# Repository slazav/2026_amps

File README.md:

A hobby project: basic electronics for my home lab (current and voltage amplifiers, current source)

https://slazav.xyz/lab/20260426-newamps.htm (RU)

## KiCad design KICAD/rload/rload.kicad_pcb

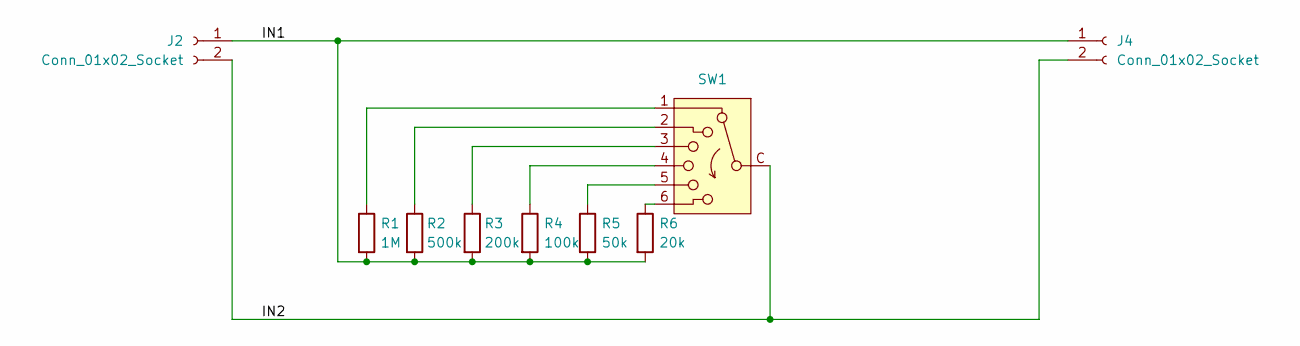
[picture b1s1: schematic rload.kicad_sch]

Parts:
J2, J4: Conn_01x02_Socket; conn_sig2
R1: 1M; R_0805_2012Metric
R2: 500k; R_0805_2012Metric
R3: 200k; R_0805_2012Metric
R4: 100k; R_0805_2012Metric
R5: 50k; R_0805_2012Metric
R6: 20k; R_0805_2012Metric
SW1: SW_Rotary_1x6_MP; switch6

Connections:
/IN1: J2.1, J4.1, R1.2, R2.2, R3.2, R4.2, R5.2, R6.2
/IN2: J2.2, J4.2, SW1.C
unnamed: R1.1, SW1.1
unnamed: R2.1, SW1.2
unnamed: R3.1, SW1.3
unnamed: R4.1, SW1.4
unnamed: R5.1, SW1.5
unnamed: R6.1, SW1.6

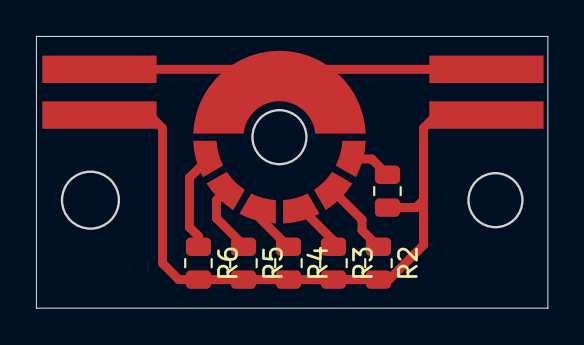
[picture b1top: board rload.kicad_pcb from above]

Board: 2 copper layers, 28.3 x 15.0 mm, 9 parts (0 on the bottom side), 8 nets.

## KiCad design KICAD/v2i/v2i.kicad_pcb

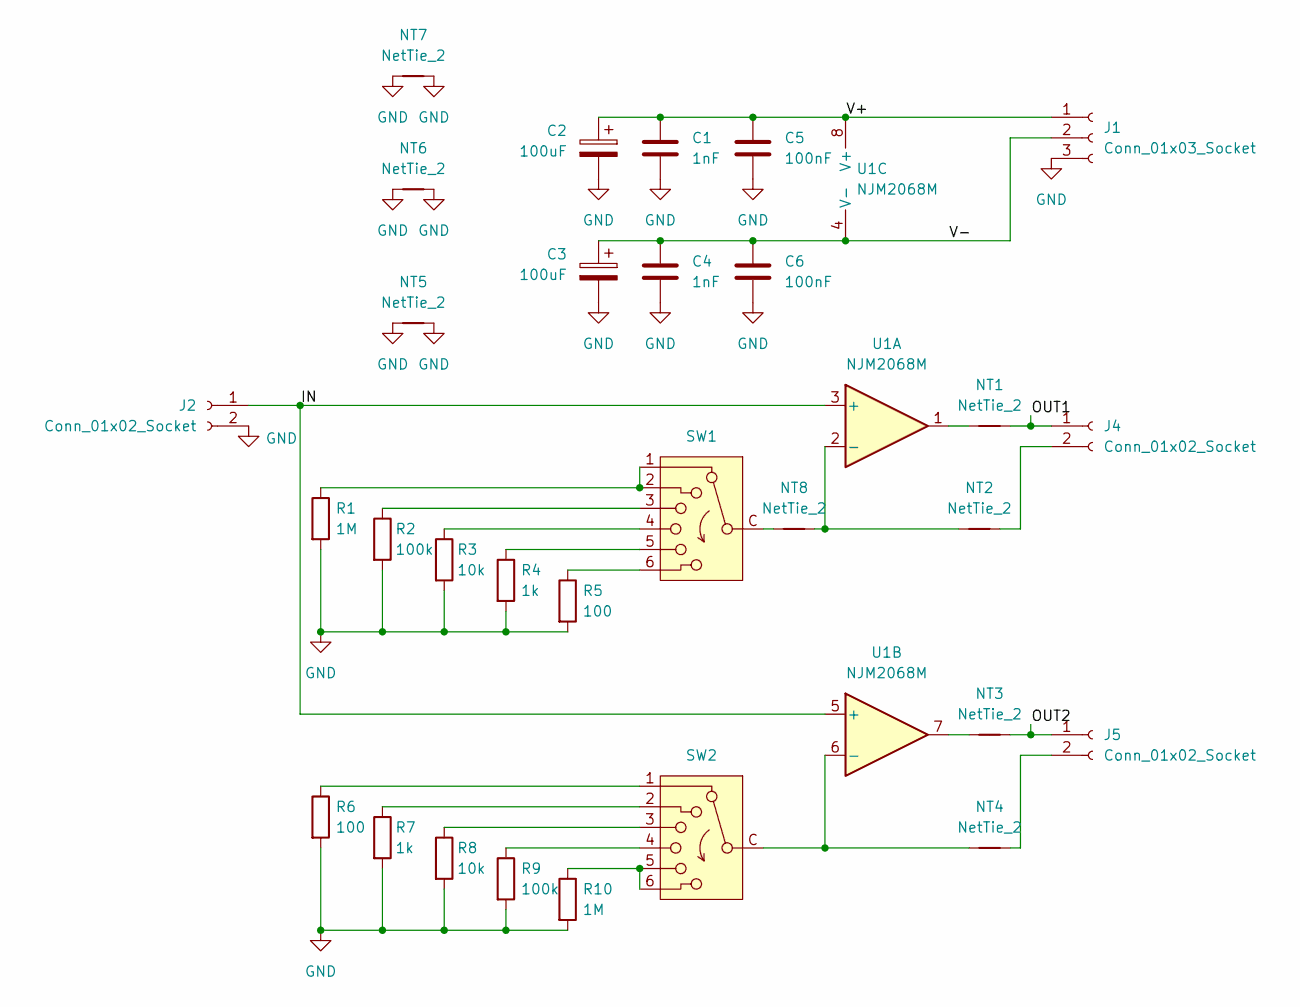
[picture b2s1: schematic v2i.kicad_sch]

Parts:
C1, C4: 1nF; C_0603_1608Metric
C2, C3: 100uF; C_1206_3216Metric
C5, C6: 100nF; C_0603_1608Metric
J1: Conn_01x03_Socket; conn_pwr3
J2, J4, J5: Conn_01x02_Socket; conn_sig2
NT1, NT2, NT3, NT4, NT5, NT6, NT7, NT8: NetTie_2; R_1206_3216Metric
R1, R10: 1M; R_0805_2012Metric
R2, R9: 100k; R_0805_2012Metric
R3, R8: 10k; R_0805_2012Metric
R4, R7: 1k; R_0805_2012Metric
R5, R6: 100; R_0805_2012Metric
SW1, SW2: SW_Rotary_1x6_MP; switch6
U1: NJM2068M; SOIC-8_5.3x5.3mm_P1.27mm

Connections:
/IN: J2.1, U1.3 (+), U1.5 (+)
/OUT1: J4.1, NT1.2
/OUT2: J5.1, NT3.2
/V+: C1.1, C2.1, C5.1, J1.1, U1.8 (V+)
/V-: C3.1, C4.1, C6.1, J1.2, U1.4 (V-)
GND: C1.2, C2.2, C3.2, C4.2, C5.2, C6.2, J1.3, J2.2, NT5.1, NT5.2, NT6.1, NT6.2, NT7.1, NT7.2, R1.2, R2.2, R3.2, R4.2, R5.2, R6.2, R7.2, R8.2, R9.2, R10.2
unnamed: J4.2, NT2.2
unnamed: J5.2, NT4.2
unnamed: NT1.1, U1.1
unnamed: NT3.1, U1.7
unnamed: NT8.1, SW1.C
unnamed: R1.1, SW1.1, SW1.2
unnamed: R2.1, SW1.3
unnamed: R3.1, SW1.4
unnamed: R4.1, SW1.5
unnamed: R5.1, SW1.6
unnamed: R6.1, SW2.1
unnamed: R7.1, SW2.2
unnamed: R8.1, SW2.3
unnamed: R9.1, SW2.4
unnamed: R10.1, SW2.5, SW2.6
unnamed: NT2.1, NT8.2, U1.2 (-)
unnamed: NT4.1, SW2.C, U1.6 (-)

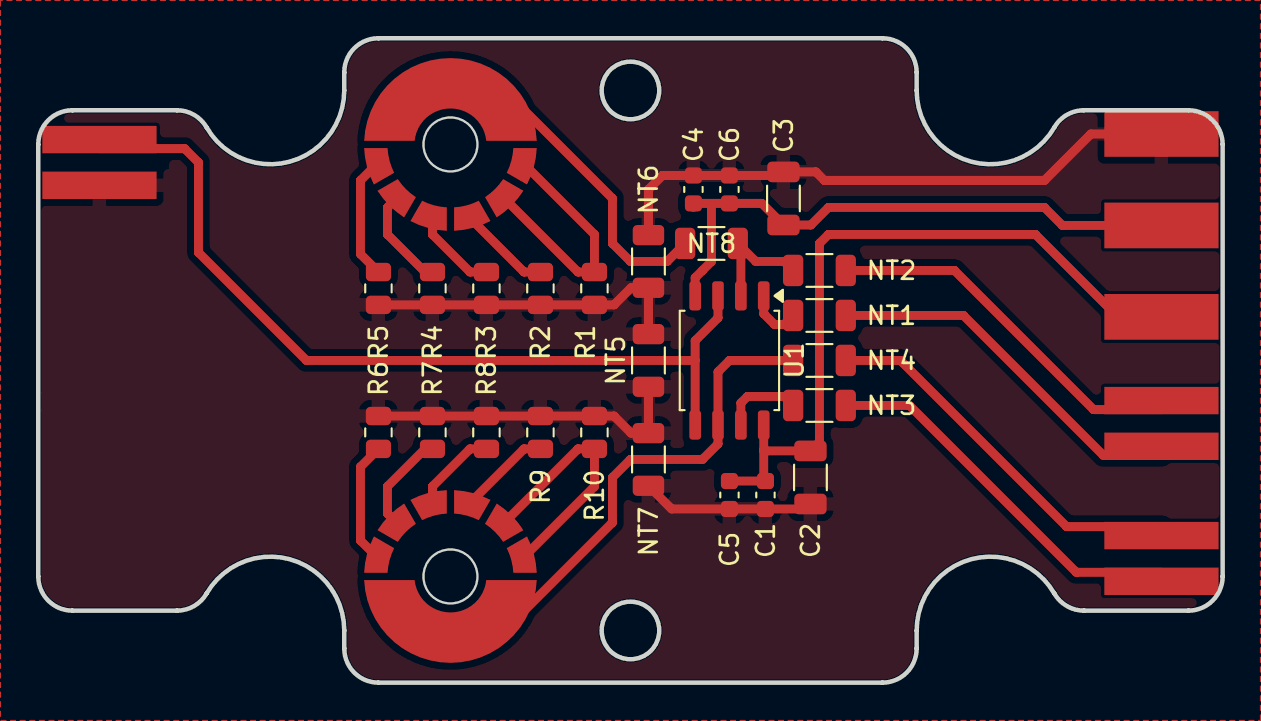
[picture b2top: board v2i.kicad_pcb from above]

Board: 2 copper layers, 65.8 x 35.8 mm, 31 parts (0 on the bottom side), 23 nets.

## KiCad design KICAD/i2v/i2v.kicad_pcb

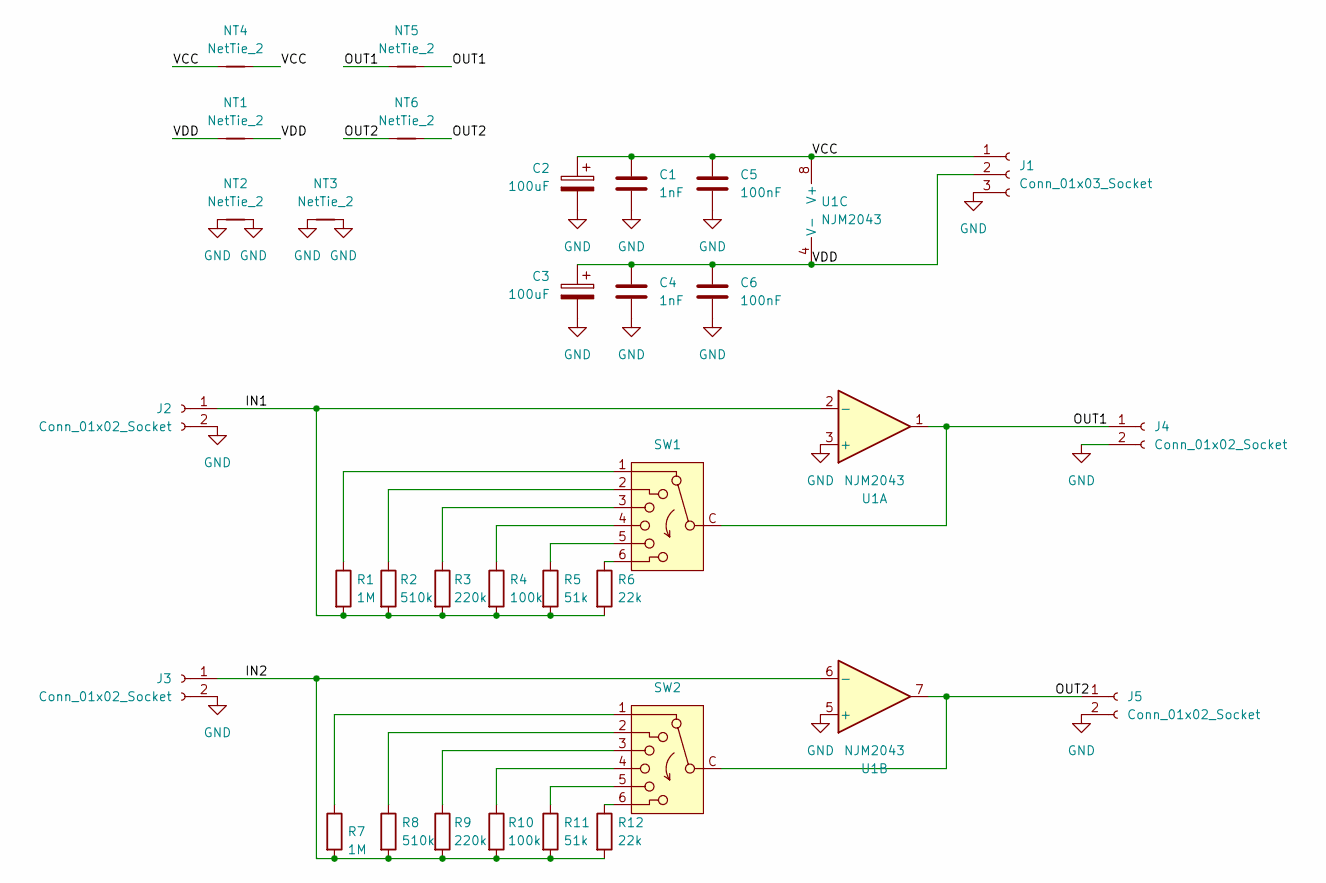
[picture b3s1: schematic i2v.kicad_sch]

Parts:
C1, C4: 1nF; C_0603_1608Metric
C2, C3: 100uF; C_1206_3216Metric
C5, C6: 100nF; C_0603_1608Metric
J1: Conn_01x03_Socket; conn_pwr3
J2, J3, J4, J5: Conn_01x02_Socket; conn_sig2
NT1, NT2, NT3, NT4, NT5, NT6: NetTie_2; R_1206_3216Metric
R1, R7: 1M; R_0805_2012Metric
R2, R8: 510k; R_0805_2012Metric
R3, R9: 220k; R_0805_2012Metric
R4, R10: 100k; R_0805_2012Metric
R5, R11: 51k; R_0805_2012Metric
R6, R12: 22k; R_0805_2012Metric
SW1, SW2: SW_Rotary_1x6_MP; switch6
U1: NJM2043; SOIC-8_5.3x5.3mm_P1.27mm

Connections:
/IN1: J2.1, R1.2, R2.2, R3.2, R4.2, R5.2, R6.2, U1.2 (-)
/IN2: J3.1, R7.2, R8.2, R9.2, R10.2, R11.2, R12.2, U1.6 (-)
/OUT1: J4.1, NT5.1, NT5.2, SW1.C, U1.1
/OUT2: J5.1, NT6.1, NT6.2, SW2.C, U1.7
/VCC: C1.1, C2.1, C5.1, J1.1, NT4.1, NT4.2, U1.8 (V+)
/VDD: C3.1, C4.1, C6.1, J1.2, NT1.1, NT1.2, U1.4 (V-)
GND: C1.2, C2.2, C3.2, C4.2, C5.2, C6.2, J1.3, J2.2, J3.2, J4.2, J5.2, NT2.1, NT2.2, NT3.1, NT3.2, U1.3 (+), U1.5 (+)
unnamed: R1.1, SW1.1
unnamed: R2.1, SW1.2
unnamed: R3.1, SW1.3
unnamed: R4.1, SW1.4
unnamed: R5.1, SW1.5
unnamed: R6.1, SW1.6
unnamed: R7.1, SW2.1
unnamed: R8.1, SW2.2
unnamed: R9.1, SW2.3
unnamed: R10.1, SW2.4
unnamed: R11.1, SW2.5
unnamed: R12.1, SW2.6

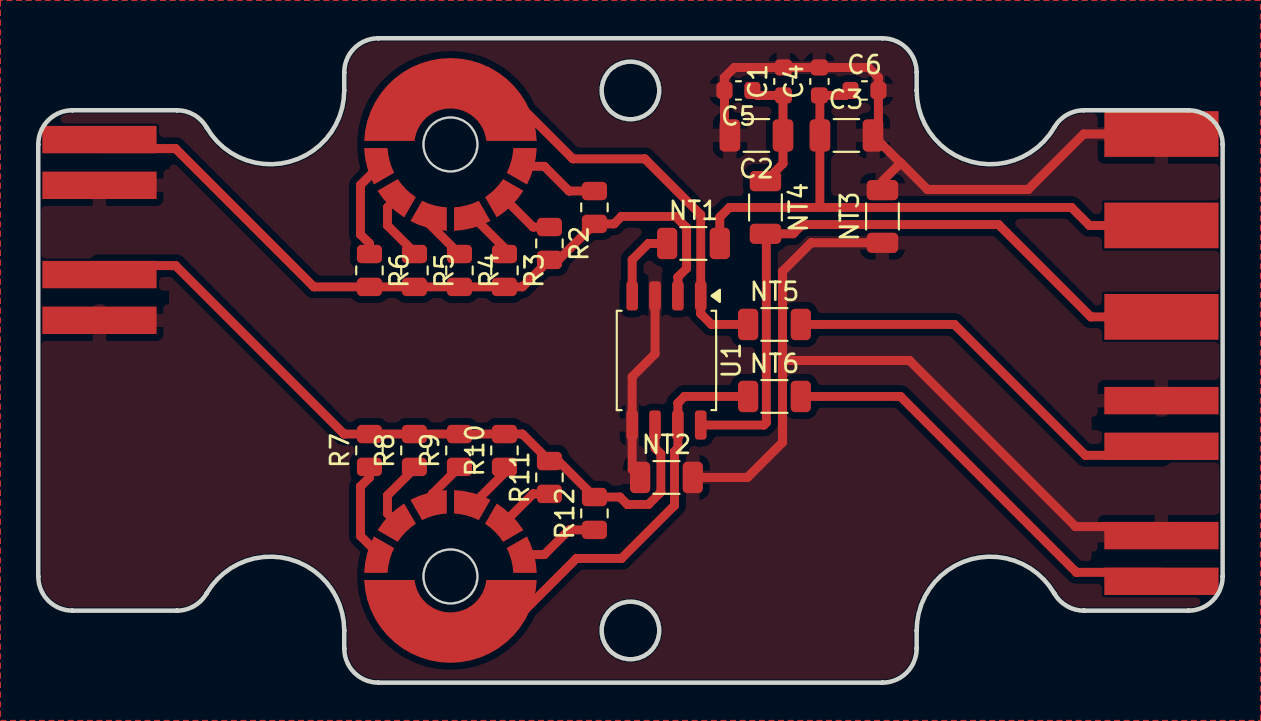
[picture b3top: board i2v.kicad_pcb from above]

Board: 2 copper layers, 65.8 x 35.8 mm, 32 parts (0 on the bottom side), 19 nets.

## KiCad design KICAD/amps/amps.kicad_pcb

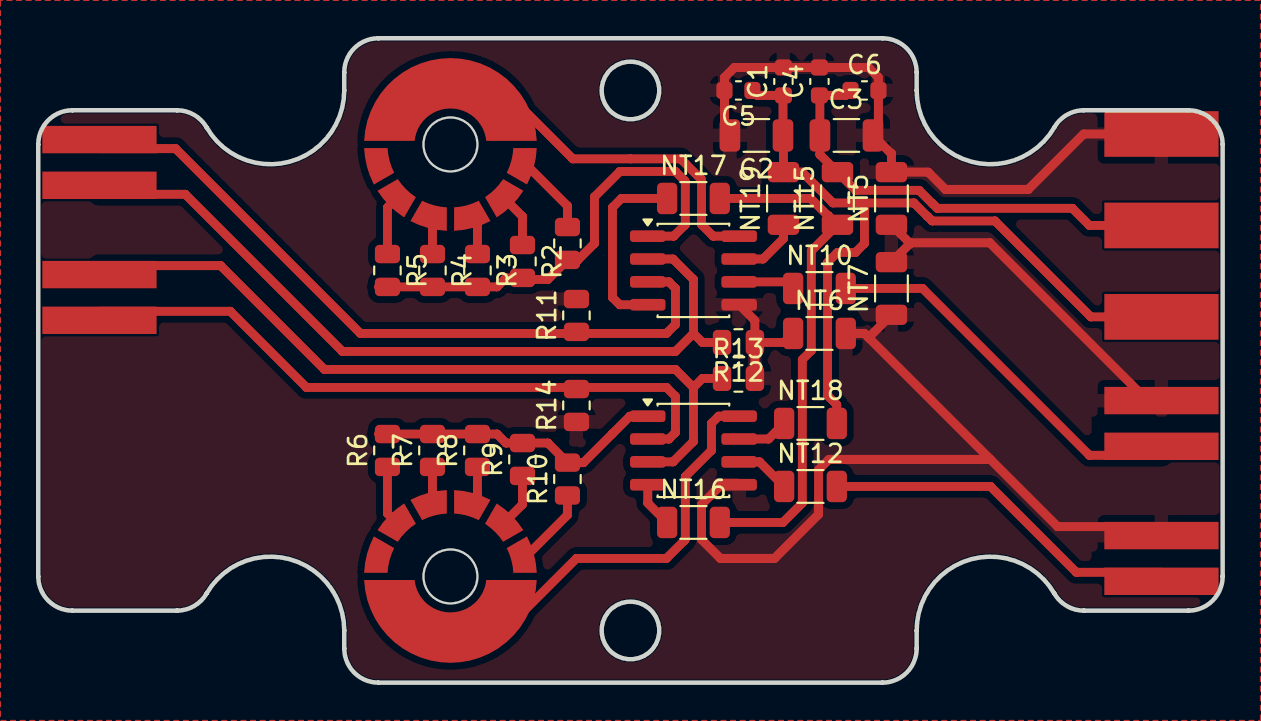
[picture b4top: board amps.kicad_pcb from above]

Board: 2 copper layers, 65.8 x 35.8 mm, 39 parts (0 on the bottom side), 25 nets.

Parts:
C1, C4: 1nF; C_0603_1608Metric
C2, C3: 100uF; C_1206_3216Metric
C5, C6: 100nF; C_0603_1608Metric
J1: Conn_01x03_Socket; conn_pwr3
J2, J3, J4, J5: Conn_01x02_Socket; conn_sig2
NT5, NT6, NT7, NT10, NT12, NT15, NT16, NT17, NT18, NT19: NetTie_2; R_1206_3216Metric
R1, R10: 5k; R_0805_2012Metric
R2, R9: 2k; R_0805_2012Metric
R3, R8: 500; R_0805_2012Metric
R4, R7: 200; R_0805_2012Metric
R5, R6: 50; R_0805_2012Metric
R11, R12, R13, R14: 1M; R_0805_2012Metric
SW1, SW2: SW_Rotary_1x6_MP; switch6
U1, U2: INA128; SOP-8_3.76x4.96mm_P1.27mm

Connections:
/IN1N: J2.2, R12.2, U1.2 (-)
/IN1P: J2.1, R11.1, U1.3 (+)
/IN2N: J3.2, R14.2, U2.2 (-)
/IN2P: J3.1, R13.1, U2.3 (+)
/OUT1: J4.1, NT10.2
/OUT2: J5.1, NT12.2
GND: C1.2, C2.2, C3.2, C4.2, C5.2, C6.2, J1.3, J4.2, J5.2, NT5.1, NT5.2, NT6.1, NT6.2, NT7.1, NT7.2, R11.2, R12.1, R13.2, R14.1, U1.5 (Ref), U2.5 (Ref)
unnamed: NT10.1, U1.6
unnamed: NT12.1, U2.6
unnamed: R1.1, SW1.1
unnamed: R1.2, R2.2, R3.2, R4.2, R5.2, U1.1 (Rg)
unnamed: R2.1, SW1.2
unnamed: R3.1, SW1.3
unnamed: R4.1, SW1.4
unnamed: R5.1, SW1.5
unnamed: R6.1, SW2.2
unnamed: R7.1, SW2.3
unnamed: R8.1, SW2.4
unnamed: R9.1, SW2.5
unnamed: R10.1, SW2.6
unnamed: R6.2, R7.2, R8.2, R9.2, R10.2, U2.1 (Rg)
unnamed: SW1.C, U1.8 (Rg)
unnamed: SW2.C, U2.8 (Rg)
VCC: C1.1, C2.1, C5.1, J1.1, NT18.1, NT18.2, NT19.1, NT19.2, U1.7 (V+), U2.7 (V+)
VDD: C3.1, C4.1, C6.1, J1.2, NT15.1, NT15.2, NT16.1, NT16.2, NT17.1, NT17.2, U1.4 (V-), U2.4 (V-)

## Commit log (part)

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2026-06-02 Add KiCAD files:
    This commit is done after making first version of the PCBs.
    A couple of fixes have been added compared to the fabricated version:
    - add missing switch pads in amps PCB
    - adjust connector pads
2026-06-02 add DXF files (boxes and PCB outlines)
2026-06-02 Create LICENSE
2026-06-02 add DXF_PCB (new version, not tested)
2026-06-02 add QUCS folder
2026-06-03 small fixes in KiCAD and DXF
2026-06-03 README.md: add link and image
2026-06-06 add measurement results for voltage amplifier
2026-06-06 remove old amplifier measurement, keep only recent one
2026-06-06 i2v measurement
2026-06-06 v2i measurements
2026-06-06 QUCS: add i2v.sch
2026-06-07 update i2v plots
2026-06-07 meas_i2v: more measurements
2026-06-28 meas_i2v_2: measurements after a few modifications of i2v device
2026-06-28 meas_i2v: update meas script
2026-06-28 meas_i2v_2: complete measurements
2026-06-28 meas_i2v: move all data to a single folder; update plots
2026-06-28 meas_amp: improved noise measurements; fix gain calculation
2026-06-28 meas_i2v: noise plot
2026-06-29 QUCS: add v2i_freq.sch; do not keep *.ngspice files
2026-06-29 meas_v2i: move data to a separate folder
2026-06-29 meas_v2i: fix headers of data files
